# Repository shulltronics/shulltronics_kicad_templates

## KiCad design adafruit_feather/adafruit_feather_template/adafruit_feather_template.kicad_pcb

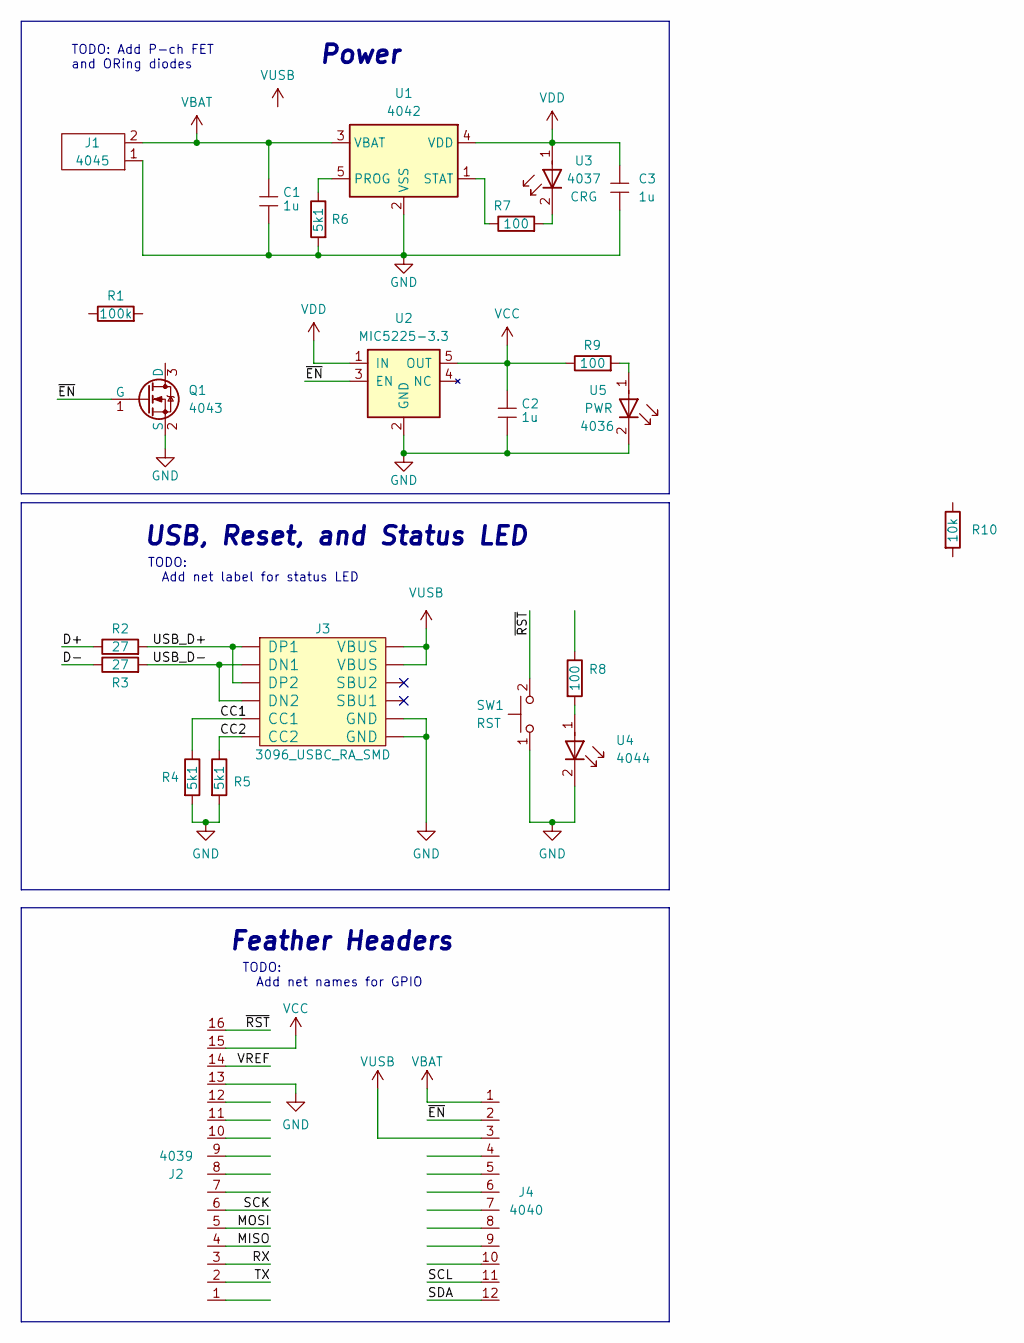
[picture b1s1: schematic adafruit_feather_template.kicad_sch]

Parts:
C1, C2, C3: 4013_Capacitor_1u_16V_0402; C_0402_HandSolder
J1: 4045_Connector_PH_2pos_RA_SMD; 4045_JST_PH_2pos_RA_SMD
J2: 4039_Header_Male_Vert_16pin_0.1in; 4039_Header_16pos_2.54mm
J3: 3096_USBC_RA_SMD; 3096_USBC_RA
J4: 4040_Header_Male_Vert_12pin_0.1in; 4040_Header_12pos_2.54mm
Q1: 4043_DMG3414_Nch_Mosfet_SOT23-3; SOT-23-3
R1: 4017_Resistor_SMD_100k_0.125W_1%_1; RES-0402
R2, R3: 4011_Resistor_SMD_27_0.125W_1%; RES-0402
R4, R5, R6: 4009_Resistor_SMD_5k1_0.10W_1%; RES-0402
R7, R8, R9: 4038_Resistor_SMD_100_0.125W_1%; RES-0402
R10: 4008_Resistor_SMD_10k_0.125W_1%; RES-0402
SW1: RST; 4012_PushButton_NO_SMD
U1: 4042_MCP73831_Battery_Charger; SOT-23-5
U2: 3093_MIC5225_3v3; 3093_MIC5225_3v3_LDO
U3: CRG; LED_0402
U4: 4044_LED_RED_SMD; LED_0402
U5: PWR; LED_0402

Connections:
/CC1: J3.A5 (CC1), R4.1
/CC2: J3.B5 (CC2), R5.1
/D+: R2.1
/D-: R3.1
/MISO: J2.4
/MOSI: J2.5
/RX: J2.3
/SCK: J2.6
/SCL: J4.11
/SDA: J4.12
/TX: J2.2
/USB_D+: J3.A6 (DP1), J3.B6 (DP2), R2.2
/USB_D-: J3.A7 (DN1), J3.B7 (DN2), R3.2
/VREF: J2.14
/~EN: J4.2, Q1.1 (G), U2.3 (EN)
/~RST: J2.16, SW1.2
GND: C1.1, C2.1, C3.1, J1.1, J2.13, J3.A1/B12 (GND), J3.B1/A12 (GND), Q1.2 (S), R4.2, R5.2, R6.2, SW1.1, U1.2 (VSS), U2.2 (GND), U4.2 (K), U5.2 (K)
unnamed: R6.1, U1.5 (PROG)
unnamed: R7.1, U1.1 (STAT)
unnamed: R7.2, U3.2 (K)
unnamed: R8.2, U4.1 (A)
unnamed: R9.2, U5.1 (A)
VBAT: C1.2, J1.2, J4.1, U1.3 (VBAT)
VCC: C2.2, J2.15, R9.1, U2.5 (OUT)
VDD: C3.2, U1.4 (VDD), U2.1 (IN), U3.1 (A)
VUSB: J3.A4/B9 (VBUS), J3.B4/A9 (VBUS), J4.3

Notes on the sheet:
TODO: Add net names for GPIO
USB, Reset, and Status LED
Feather Headers
Power
TODO: Add P-ch FET and ORing diodes
TODO: Add net label for status LED

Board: 2 copper layers, 24 parts (0 on the bottom side), 16 nets, no tracks yet.

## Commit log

2022-03-18 Started work on Adafruit Feather template
2022-03-19 Added some more of the LiPo circuitry, LEDs, and connectors
2022-03-21 Added template icon and info file
2022-03-22 Added eurorack 1u 22hp template (needs to be made generic), updated icon for feather template
